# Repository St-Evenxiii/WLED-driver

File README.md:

# WLED ESP32-WROOM-32D driver for a 16x16 matrix

KiCad design files and a bring-up sketch for a carrier board that runs
[WLED](https://kno.wled.ge/) on a 16x16 5 V WS2812B matrix. An ESP32-WROOM-32D
38-pin DevKit plugs into the board.

## What's on the board

| Ref | Part | Notes |
|-----|------|-------|
| J1, J2 | 2x 1x19 female header, 2.54 mm | ESP32 38-pin DevKit, rows 25.4 mm (1.0") apart |
| U1 | **SN74HCT125N** (DIP-14) | 3.3 V GPIO16 to 5 V data. Must be **HCT**: 74LS/74HC parts won't reliably drive WS2812B from 3.3 V |
| R1 | 330 Ω axial | Series resistor at the driver output |
| C1 | 1000 µF, ≥10 V electrolytic, 10 mm dia. | Bulk cap across the LED supply |
| C2 | 100 nF ceramic | U1 decoupling |
| D1 | 1N5819 Schottky (DO-41) | +5V rail to DevKit 5V pin. Stops USB from trying to power the matrix |
| J3 | 2-pin 5.08 mm screw terminal | **Power in**: +5V, GND |
| J4 | 3-pin 5.08 mm screw terminal | **To matrix**: +5V, DIN, GND |
| H1–H4 | M3 mounting holes | |

Board size: 50 x 115 mm, 2 layers. All nets are routed. There are GND pours on
both layers, a +5V pour around the terminals, a copper keep-out under the ESP32
antenna, and a 15 x 15 mm logo area on the front silkscreen (above the antenna
end of the DevKit).

## Repository layout

```
pcb/
  generate_schematic.py   SKiDL source of truth -> wled_driver.net
  layout_board.py         netlist -> placed, routed, poured wled_driver.kicad_pcb
  check_board.py          DRC + netlist parity + design sanity checks
  netlist.py              small KiCad netlist reader used by the two scripts above
  wled_driver.kicad_pro / .kicad_pcb / .net
firmware/
  test_matrix/            Arduino sketch (folder name matches the .ino, as the IDE requires)
  tests/                  host-side tests: mock FastLED + unit tests, `make -C firmware/tests`
.github/workflows/ci.yml  runs all of the above on every push
```

## Testing

```sh
# Firmware logic (any machine with g++)
make -C firmware/tests

# PCB: DRC (with zone refill), netlist parity, sanity checks (needs KiCad's Python)
python3 pcb/check_board.py --report drc.rpt

# Regenerate from source (only if you change the design)
KICAD7_SYMBOL_DIR=/usr/share/kicad/symbols python3 pcb/generate_schematic.py   # needs: pip install skidl
python3 pcb/layout_board.py
```

Current results: ERC 0 errors / 0 warnings. DRC 0 errors and 0 unconnected
items. All 29 connected pads match the netlist. The only DRC warnings are
"library not in fp-lib-table", which happens when the check runs headless
without a KiCad library table.

## Using it

1. Open `pcb/wled_driver.kicad_pro` in KiCad 7, 8 or 9 and go to the PCB Editor.
   KiCad 8/9 will offer to upgrade the file format. Accepting is fine.
   There's no `.kicad_sch`, because the circuit is defined in `generate_schematic.py`.
   **Measure your DevKit first:** some 38-pin boards have rows 22.86 mm (0.9")
   apart, not 25.4 mm. If yours does, change `J2`'s x position in
   `layout_board.py` and regenerate.
2. Flash `firmware/test_matrix/test_matrix.ino` (board "ESP32 Dev Module",
   library FastLED). Open the Serial Monitor at 115200. The sketch shows:
   - corner markers (orientation and origin)
   - solid R/G/B (`COLOR_ORDER`)
   - a single pixel walking the chain (dead LEDs / joints)
   - row and column sweeps (`SERPENTINE`)
   - a rainbow
   - a current-limited full-white load test
3. Flash WLED and set: LED output **GPIO16**, WS2812B, 256 LEDs. Under
   *2D Configuration*, set a 16x16 matrix (serpentine for most panels).
   Leave **ABL (current limiter)** on, sized to your supply.

## Power notes

- A 16x16 WS2812B panel can draw ~15 A at full white. The J3→J4 path is a
  3 mm track inside a +5V pour, with GND poured on both layers. Plan on a few
  amps through the board on 1 oz copper (more with 2 oz). For higher current,
  inject power straight from the PSU into the matrix and use J4's +5V only as
  a local feed. Fuse the supply line in either case.
- Keep the WLED/FastLED current limit on (the sketch defaults to 2 A).
- With D1 fitted, the DevKit runs from the 5 V rail (about 4.7 V after the
  diode) or from USB, and USB never feeds the matrix.
- Mechanical: C1 is tall (~20 mm). It sits about 20 mm below the DevKit's USB
  connector. Check that your USB plug clears it, or lay C1 on its side.

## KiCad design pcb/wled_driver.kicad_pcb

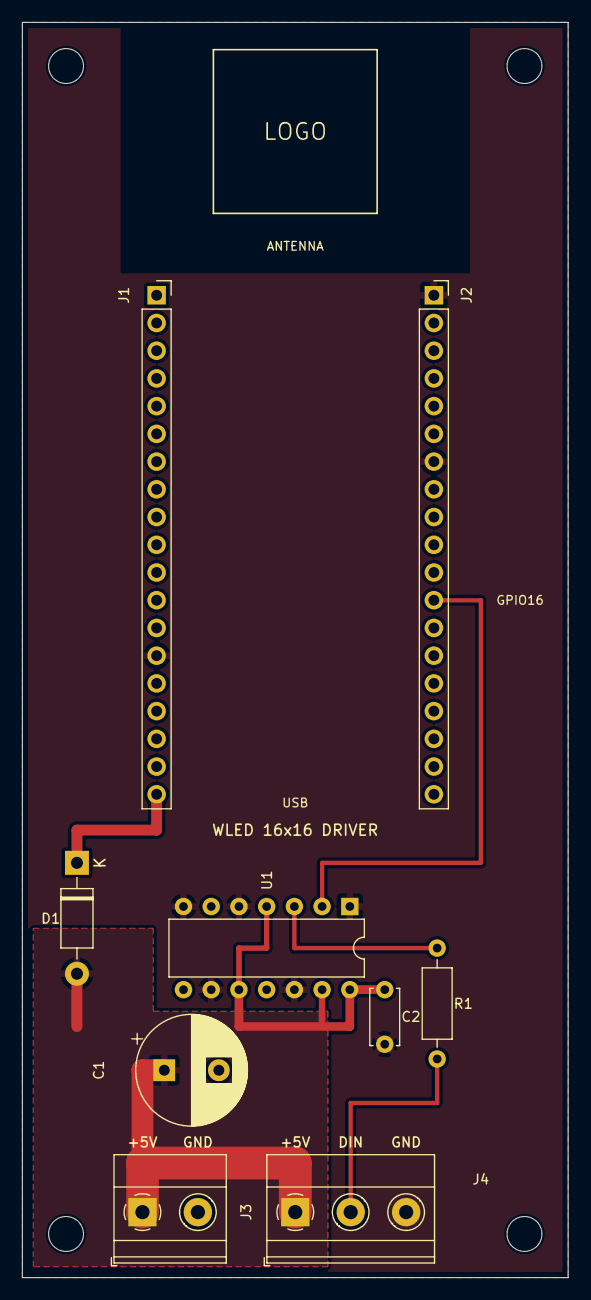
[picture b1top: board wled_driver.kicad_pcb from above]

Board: 2 copper layers, 50.0 x 115.0 mm, 13 parts (0 on the bottom side), 6 nets.

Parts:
C1: 1000uF/10V; CP_Radial_D10.0mm_P5.00mm
C2: 100nF; C_Disc_D5.0mm_W2.5mm_P5.00mm
D1: 1N5819; D_DO-41_SOD81_P10.16mm_Horizontal
H1, H2, H3, H4: M3; MountingHole_3.2mm_M3
J1: ESP32_DevKit_L; PinSocket_1x19_P2.54mm_Vertical
J2: ESP32_DevKit_R; PinSocket_1x19_P2.54mm_Vertical
J3: 5V_IN; TerminalBlock_Phoenix_MKDS-1,5-2-5.08_1x02_P5.08mm_Horizont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
J4: MATRIX_OUT; TerminalBlock_Phoenix_MKDS-1,5-3-5.08_1x03_P5.08mm_Horizont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
R1: 330R; R_Axial_DIN0207_L6.3mm_D2.5mm_P10.16mm_Horizontal
U1: 74HCT125; DIP-14_W7.62mm

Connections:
+5V: C1.1, C2.1, D1.2, J3.1, J4.1, U1.4, U1.10, U1.13, U1.14
DATA_3V3: J2.12, U1.2
DATA_5V: R1.1, U1.3
DATA_OUT: J4.2, R1.2
ESP_5V: D1.1, J1.19
GND: C1.2, C2.2, J1.14, J2.1, J2.7, J3.2, J4.3, U1.1, U1.5, U1.7, U1.9, U1.12
